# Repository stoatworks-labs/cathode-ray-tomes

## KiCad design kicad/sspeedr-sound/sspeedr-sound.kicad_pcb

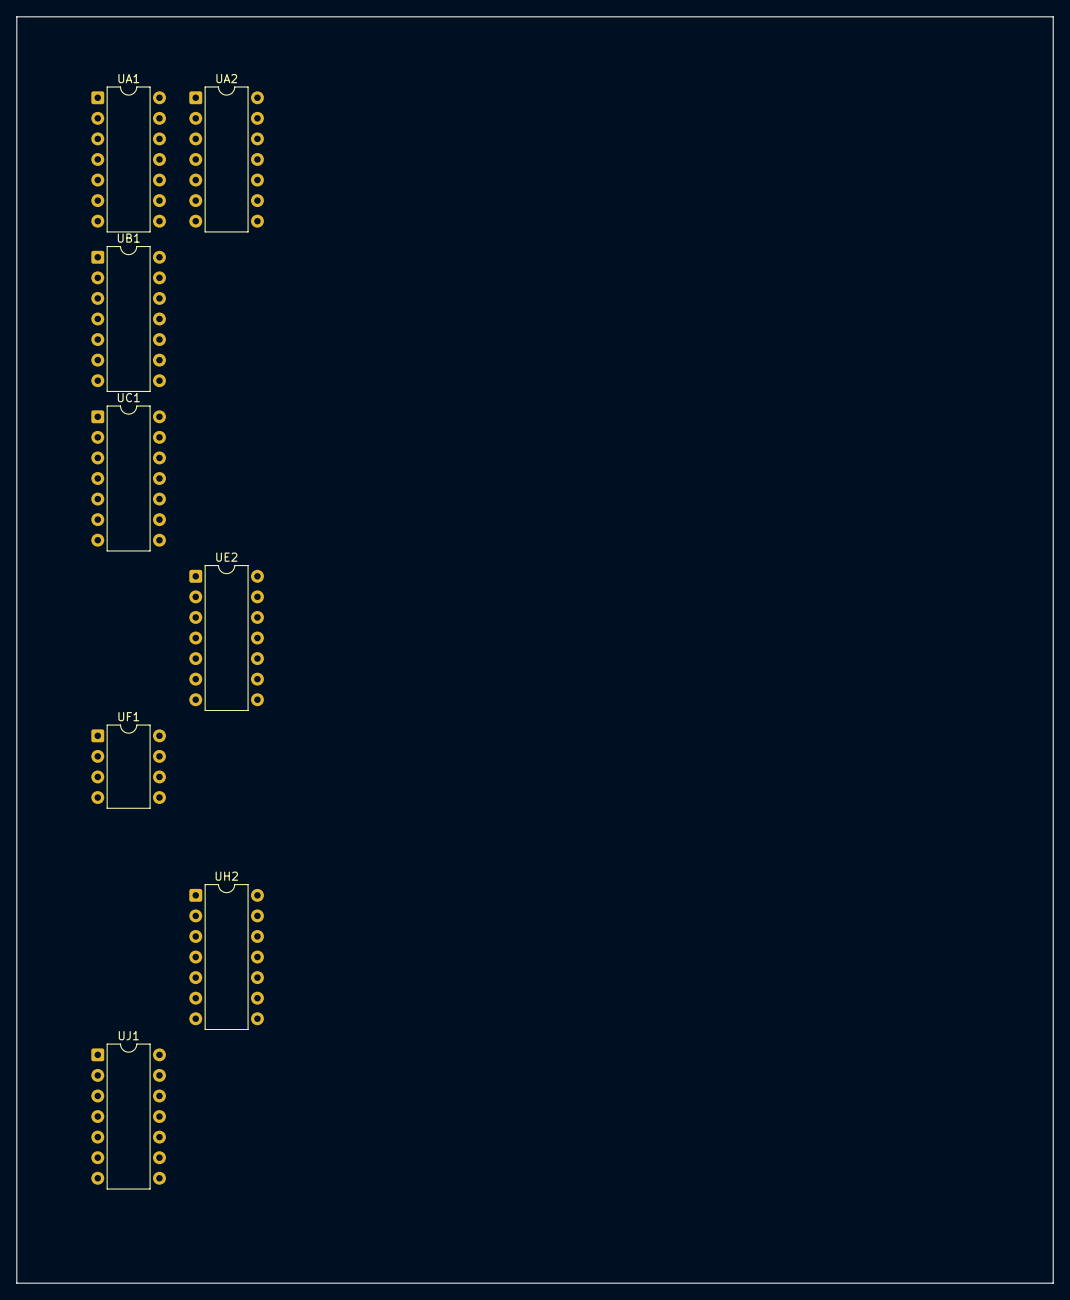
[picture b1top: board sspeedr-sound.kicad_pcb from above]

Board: 2 copper layers, 128.0 x 156.4 mm, 8 parts (0 on the bottom side), 14 nets, no tracks yet.

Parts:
UA1: LM3900; DIP-14_W7.62mm
UA2: CD4016; DIP-14_W7.62mm
UB1: CD4016; DIP-14_W7.62mm
UC1: LM3900; DIP-14_W7.62mm
UE2: CD4016; DIP-14_W7.62mm
UF1: MC3340; DIP-8_W7.62mm
UH2: LM3900; DIP-14_W7.62mm
UJ1: LM3900; DIP-14_W7.62mm

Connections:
+5V: UA1.14, UA2.14, UB1.14, UC1.14, UE2.14, UF1.8, UH2.14
GND: UA1.7, UA2.1, UA2.7, UB1.7, UC1.7, UE2.7, UF1.3, UH2.7, UJ1.7
NOISE_CR_1: UE2.5, UE2.12
unnamed: UE2.10, UH2.9
unnamed: UE2.8, UH2.4
unnamed: UA2.3, UA2.8
unnamed: UE2.4, UJ1.4
unnamed: UA1.5, UB1.13
unnamed: UA1.10, UB1.5
unnamed: UB1.12, UC1.5
unnamed: UA2.4, UC1.11
unnamed: UA1.2, UB1.2
unnamed: UA1.13, UB1.3
unnamed: UB1.11, UC1.2

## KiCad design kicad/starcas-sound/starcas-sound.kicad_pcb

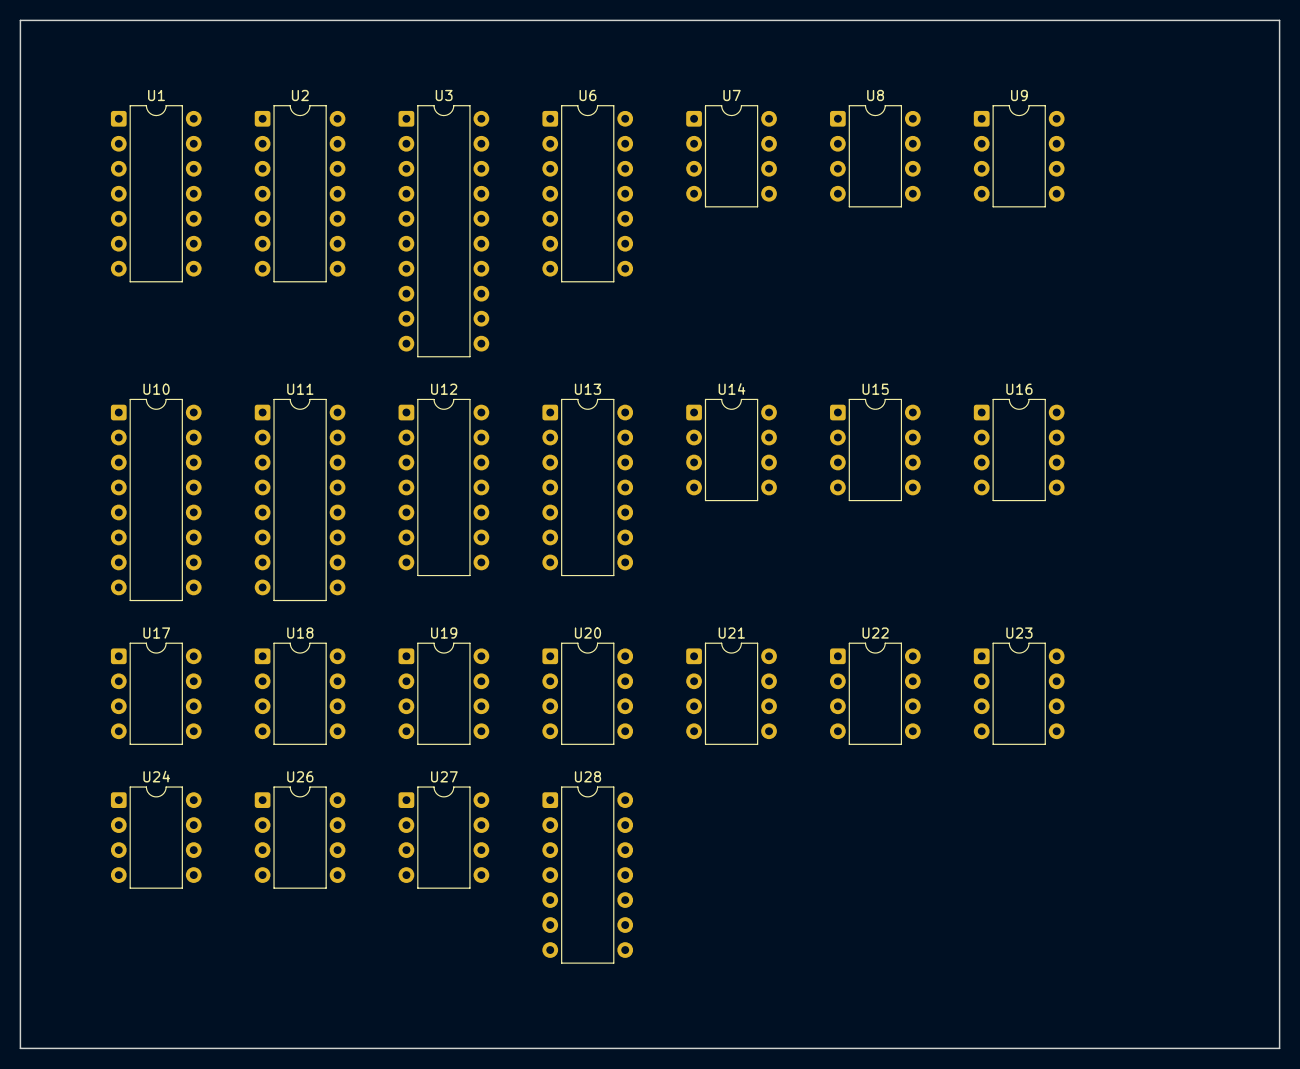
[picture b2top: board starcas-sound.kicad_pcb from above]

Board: 2 copper layers, 128.0 x 104.5 mm, 25 parts (0 on the bottom side), 37 nets, no tracks yet.

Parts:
U1: 7414; DIP-14_W7.62mm
U2: 74LS164; DIP-14_W7.62mm
U3: 74LS377; DIP-20_W7.62mm
U6: 7406; DIP-14_W7.62mm
U7, U8, U15, U26, U27: TL081; DIP-8_W7.62mm
U9, U17: LM566; DIP-8_W7.62mm
U10, U11: 74LS163; DIP-16_W7.62mm
U12, U13: 74LS393; DIP-14_W7.62mm
U14: S2688; DIP-8_W7.62mm
U16, U23, U24: LM555; DIP-8_W7.62mm
U18, U19, U20, U21, U22: CA3080; DIP-8_W7.62mm
U28: 74LS107; DIP-14_W7.62mm

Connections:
+5V: U1.14, U2.14, U3.20, U6.14, U10.16, U11.16, U12.14, U13.14, U16.4, U16.8, U23.8, U24.8, U28.14
+15V: U7.7, U8.7, U14.4, U15.7, U17.8, U18.7, U19.7, U20.7, U21.7, U22.7, U26.7, U27.7
-15V: U7.4, U8.4, U9.1, U15.4, U18.4, U19.4, U20.4, U21.4, U22.4, U26.4, U27.4
BACKGROUND_EN: U3.12, U6.1, U13.2
BL0: U3.19, U6.13
BL1: U3.16, U6.11
BL2: U3.15, U6.9
CLK: U10.2, U11.2, U13.1, U28.12
GND: U1.7, U2.7, U3.1, U3.10, U6.7, U7.3, U9.8, U10.4, U10.5, U10.6, U10.8, U11.3, U11.4, U11.8, U12.7, U12.12, U13.7, U13.12, U14.1, U14.2, U16.1, U17.1, U23.1, U24.1, U27.3, U28.4, U28.7
HI: U2.2, U2.9, U10.3, U10.7, U10.10, U11.5, U11.6, U11.7
NOISE: U15.2, U15.6
unnamed: U16.2, U16.6
unnamed: U23.2, U23.6
unnamed: U24.2, U24.6
unnamed: U26.2, U26.6
unnamed: U6.2, U10.1, U11.1
unnamed: U18.6, U19.6, U20.6, U21.6, U22.6, U26.3
unnamed: U1.1, U1.12
unnamed: U1.2, U2.1
unnamed: U1.4, U3.11
unnamed: U1.5, U1.8
unnamed: U1.6, U2.8
unnamed: U1.3, U1.10
unnamed: U2.3, U3.3
unnamed: U2.4, U3.4
unnamed: U2.5, U3.7
unnamed: U2.6, U3.8
unnamed: U2.10, U3.13
unnamed: U2.11, U3.14
unnamed: U2.12, U3.17
unnamed: U2.13, U3.18
unnamed: U10.9, U11.9, U12.13, U28.2
unnamed: U10.15, U11.10
unnamed: U11.15, U28.1, U28.13
unnamed: U13.6, U13.13
OUT_3: U6.5, U12.2
STAR_EN: U3.6, U23.4, U24.4

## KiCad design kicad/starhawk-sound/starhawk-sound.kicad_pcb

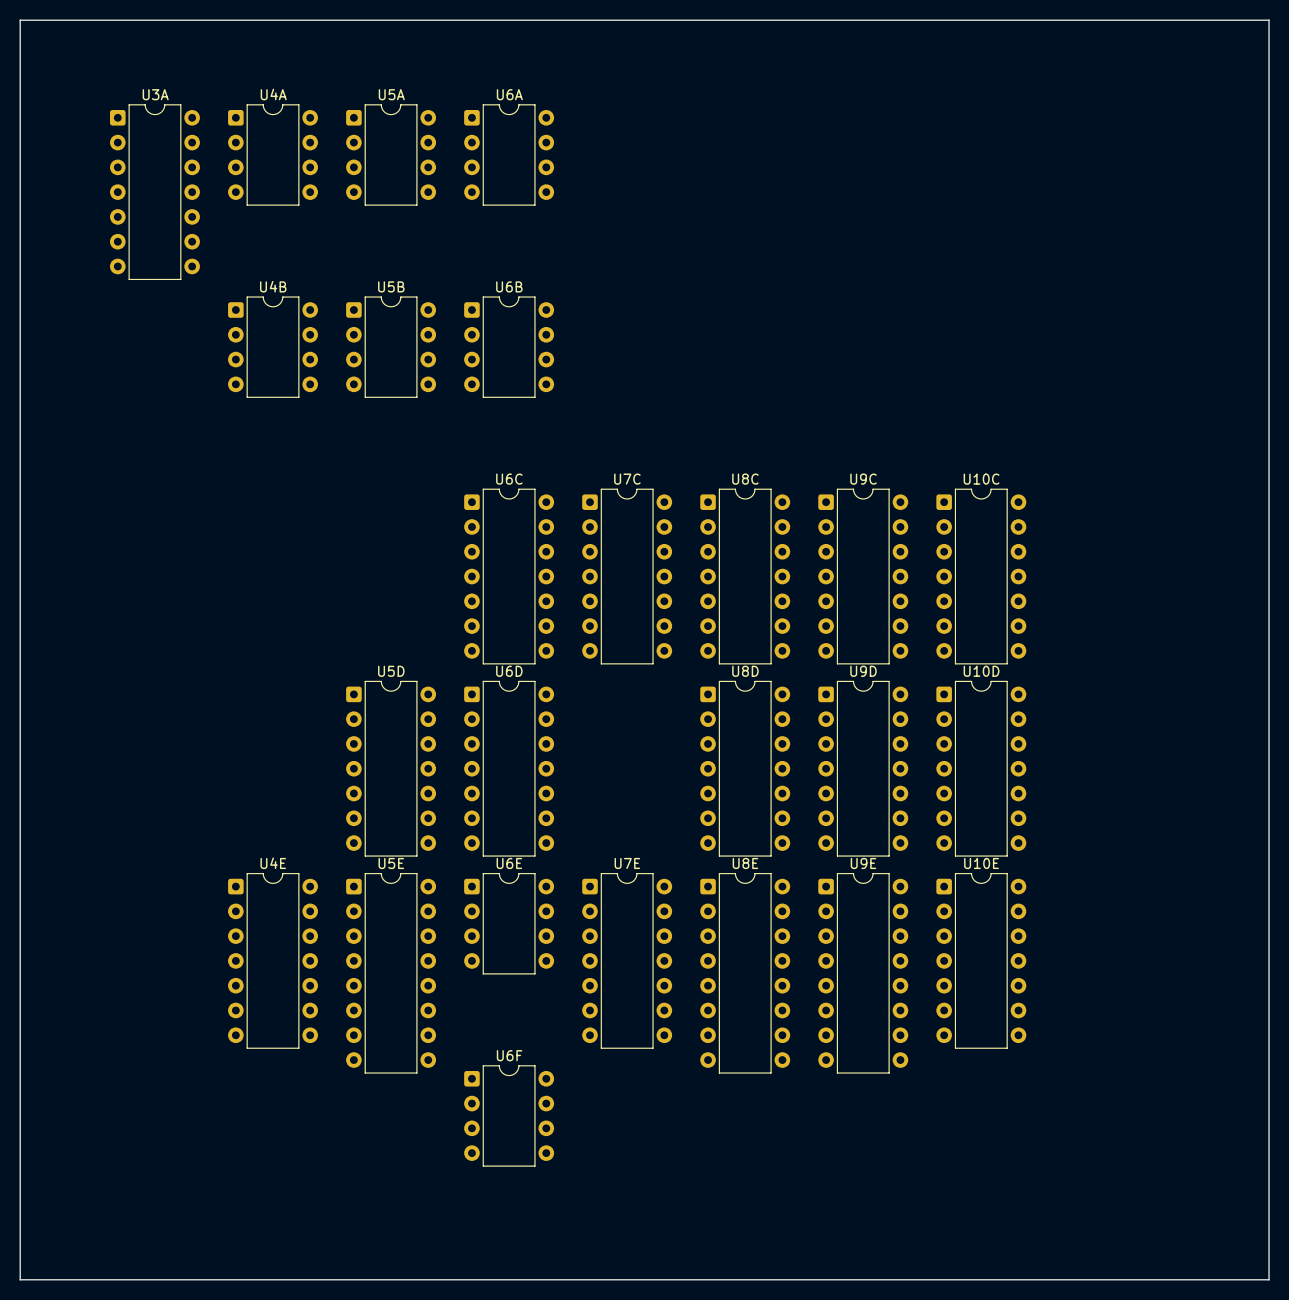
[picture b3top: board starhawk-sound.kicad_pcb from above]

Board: 2 copper layers, 128.0 x 129.1 mm, 25 parts (0 on the bottom side), 53 nets, no tracks yet.

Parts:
U3A: TL182; DIP-14_W7.62mm
U4A, U4B, U5A, U5B, U6B, U6E, U6F: TL081; DIP-8_W7.62mm
U4E, U7E, U10E: 74LS393; DIP-14_W7.62mm
U5D, U6D: LM556; DIP-14_W7.62mm
U5E, U8E: 74S287; DIP-16_W7.62mm
U6A: CA3080; DIP-8_W7.62mm
U6C: 74LS04; DIP-14_W7.62mm
U7C: 7406; DIP-14_W7.62mm
U8C, U8D, U9C, U9D: 74LS164; DIP-14_W7.62mm
U9E: 74LS163; DIP-16_W7.62mm
U10C: 74LS86; DIP-14_W7.62mm
U10D: 74LS21; DIP-14_W7.62mm

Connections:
+5V: U3A.7, U4E.14, U5E.16, U6C.14, U6D.4, U6D.10, U6D.14, U7C.14, U7E.14, U8C.9, U8C.14, U8D.9, U8D.14, U8E.16, U9C.9, U9C.14, U9D.9, U9D.14, U9E.1, U9E.7, U9E.9, U9E.10, U9E.16, U10C.14, U10D.14, U10E.14
+15V: U3A.6, U4A.7, U4B.7, U5A.7, U5B.7, U5D.4, U5D.14, U6A.7, U6B.7, U6E.7, U6F.7
-15V: U3A.9, U4A.4, U4B.4, U5A.4, U5B.4, U6A.4, U6B.4, U6E.4, U6F.4
GND: U3A.8, U4A.3, U4E.2, U4E.7, U4E.12, U5A.3, U5B.3, U5D.7, U5E.1, U5E.8, U5E.13, U6B.3, U6C.7, U6D.7, U7C.7, U7E.2, U7E.7, U7E.12, U8C.7, U8D.7, U8E.1, U8E.8, U8E.13, U9C.7, U9D.7, U9E.8, U10C.7, U10D.7, U10E.7
unnamed: U6D.12, U6D.13
unnamed: U6D.2, U6D.6
unnamed: U3A.1, U4A.2
unnamed: U5D.2, U5D.6
unnamed: U3A.14, U6A.6
unnamed: U4E.1, U6C.12
unnamed: U4E.3, U5E.7
unnamed: U4E.4, U5E.4
unnamed: U4E.5, U5E.6
unnamed: U4E.8, U5E.15
unnamed: U4E.10, U5E.2
unnamed: U4E.11, U5E.3
unnamed: U4E.6, U4E.13, U5E.5
unnamed: U5E.14, U6C.2, U7C.13
unnamed: U6C.4, U7C.11
unnamed: U6C.6, U7C.9, U8E.14
unnamed: U6C.8, U7E.1
unnamed: U7E.3, U8E.7
unnamed: U7E.4, U8E.4
unnamed: U7E.5, U8E.6
unnamed: U7E.8, U8E.15
unnamed: U7E.10, U8E.2
unnamed: U7E.11, U8E.3
unnamed: U7E.6, U7E.13, U8E.5
unnamed: U8C.13, U9C.1, U9C.2
unnamed: U8D.13, U9D.1, U9D.2
unnamed: U10C.1, U10D.8
unnamed: U10C.2, U10C.8
unnamed: U8C.1, U8C.2, U10C.3
unnamed: U10C.5, U10D.6
unnamed: U8D.1, U8D.2, U10C.6
unnamed: U9C.12, U10C.9
unnamed: U9C.10, U10C.10
unnamed: U10C.4, U10C.11
unnamed: U9D.12, U10C.12
unnamed: U9D.10, U10C.13
unnamed: U10D.1, U10E.3
unnamed: U10D.2, U10E.4
unnamed: U10D.4, U10E.5
unnamed: U10D.5, U10E.6
unnamed: U10D.9, U10E.8
unnamed: U10D.10, U10E.9
unnamed: U10D.12, U10E.10
unnamed: U10D.13, U10E.11
unnamed: U6D.5, U8D.8, U9D.8, U9E.2, U10E.1
unnamed: U8D.3, U10E.2
unnamed: U8C.3, U10E.12
unnamed: U8C.8, U9C.8, U9E.15, U10E.13
OUT_3: U3A.5, U6C.3

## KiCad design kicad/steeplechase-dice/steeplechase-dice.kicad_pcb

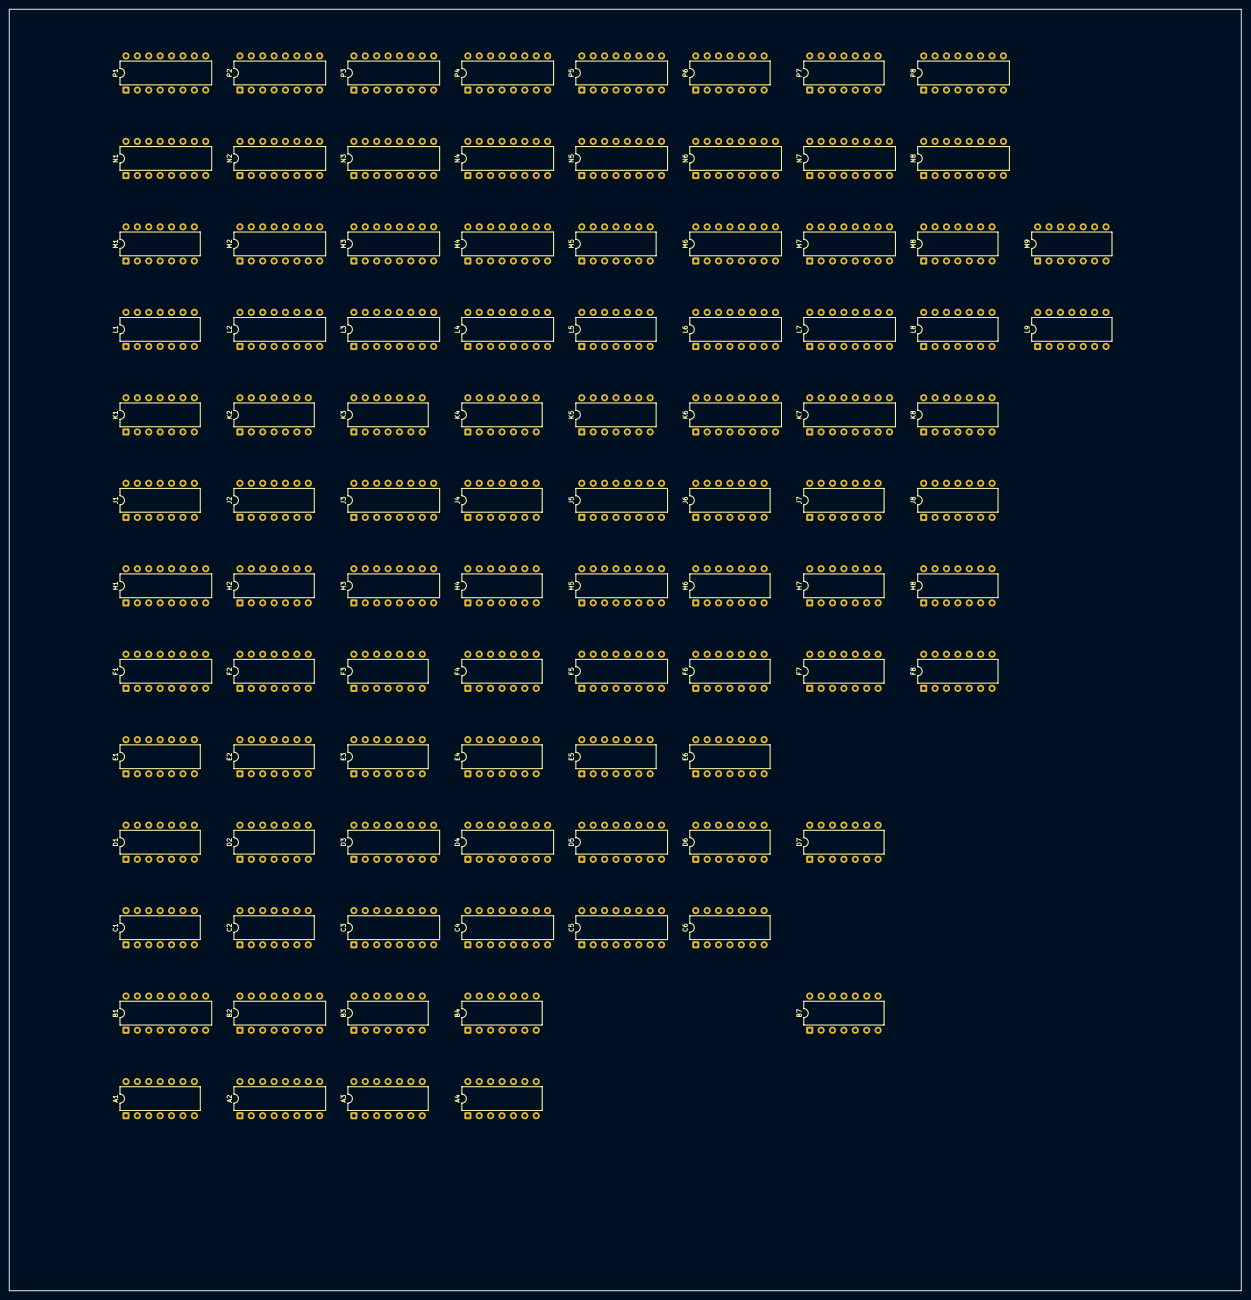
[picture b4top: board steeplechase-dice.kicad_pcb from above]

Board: 2 copper layers, 274.6 x 285.6 mm, 94 parts (0 on the bottom side), 273 nets, no tracks yet.

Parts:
A1: 74164; DIP-14_W7.62mm
A2: 9316; DIP-16_W7.62mm
A3: 7400; DIP-14_W7.62mm
A4: 7474; DIP-14_W7.62mm
B1, B2: 9316; DIP-16_W7.62mm
B3: 7420; DIP-14_W7.62mm
B4: 7408; DIP-14_W7.62mm
B7: 74107; DIP-14_W7.62mm
C1: 74164; DIP-14_W7.62mm
C2: 7474; DIP-14_W7.62mm
C3: 9316; DIP-16_W7.62mm
C4: 74S287; DIP-16_W7.62mm
C5: 74165; DIP-16_W7.62mm
C6: 7420; DIP-14_W7.62mm
D1, D7: 7400; DIP-14_W7.62mm
D2, D6: 7404; DIP-14_W7.62mm
D3: 9316; DIP-16_W7.62mm
D4: 74S287; DIP-16_W7.62mm
D5: 74165; DIP-16_W7.62mm
E1, E2, E3, E5: 7474; DIP-14_W7.62mm
E4, E6: 7402; DIP-14_W7.62mm
F1: 9316; DIP-16_W7.62mm
F2: 7427; DIP-14_W7.62mm
F3: 7410; DIP-14_W7.62mm
F4: 7486; DIP-14_W7.62mm
F5: 9312; DIP-16_W7.62mm
F6, F8: 7474; DIP-14_W7.62mm
F7: 7493; DIP-14_W7.62mm
H1, H3: 9316; DIP-16_W7.62mm
H2: 7474; DIP-14_W7.62mm
H4: 7400; DIP-14_W7.62mm
H5: 9312; DIP-16_W7.62mm
H6, H7: 7402; DIP-14_W7.62mm
H8: 7404; DIP-14_W7.62mm
J1: 7432; DIP-14_W7.62mm
J2: 7402; DIP-14_W7.62mm
J3: 9301; DIP-16_W7.62mm
J4: 7474; DIP-14_W7.62mm
J5: 9312; DIP-16_W7.62mm
J6, J7: 7411; DIP-14_W7.62mm
J8: 7486; DIP-14_W7.62mm
K1, K5, K8: 7474; DIP-14_W7.62mm
K2, K4: 7402; DIP-14_W7.62mm
K3: 7404; DIP-14_W7.62mm
K6, K7: 9316; DIP-16_W7.62mm
L1: 7404; DIP-14_W7.62mm
L2, L3, L4, L6, L7: 9316; DIP-16_W7.62mm
L5, L8: 7474; DIP-14_W7.62mm
L9: 7414; DIP-14_W7.62mm
M1, M9: 7404; DIP-14_W7.62mm
M2, M3, M4, M6, M7: 9316; DIP-16_W7.62mm
M5, M8: 7474; DIP-14_W7.62mm
N1, N2, N3, N4: 9316; DIP-16_W7.62mm
N5: 9301; DIP-16_W7.62mm
N6, N7: 74175; DIP-16_W7.62mm
N8: 9312; DIP-16_W7.62mm
P1, P2, P3, P4, P5: 9316; DIP-16_W7.62mm
P6: 7430; DIP-14_W7.62mm
P7: 7404; DIP-14_W7.62mm
P8: 9312; DIP-16_W7.62mm

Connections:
+5V: A1.14, A2.16, A3.14, A4.14, B1.16, B2.16, B3.14, B4.14, B7.14, C1.14, C2.14, C3.16, C5.16, C6.14, D1.14, D2.14, D3.16, D5.16, D6.14, D7.14, E1.14, E2.14, E3.14, E4.14, E5.14, E6.14, F1.16, F2.14, F3.14, F4.14, F5.16, F6.14, F7.5, F8.14, H1.16, H2.14, H3.16, H4.14, H5.16, H6.14, H7.14, H8.14, J1.14, J2.14, J3.16, J4.14, J5.16, J6.14, J7.14, J8.14, K1.14, K2.14, K3.14, K4.14, K5.14, K6.16, K7.16, K8.14, L1.14, L2.16, L3.16, L4.16, L5.14, L6.16, L7.16, L8.14, L9.14, M1.14, M2.16, M3.16, M4.16, M5.14, M6.16, M7.16, M8.14, M9.14, N1.16, N2.16, N3.16, N4.16, N5.16, N6.16, N7.16, N8.16, P1.16, P2.16, P3.16, P4.16, P5.16, P6.14, P7.14, P8.16
A: N6.10, P5.6
A1-1: A1.1, A1.2, F4.3
A1-8: A1.8, B1.9, C1.8, D1.8
A1-11: A1.11, B1.6, F4.1
A2-7: A2.7, A2.10, C2.9
A2-15: A2.15, B2.7, B2.10, D1.10
A3-3: A3.3, B4.12
A3-5: A3.5, A3.8
A3-6: A3.6, B3.10
A3-11: A3.11, B3.12
A3-13: A3.13, F4.8
A4-2: A4.2, F2.8
A4-3: A4.3, F2.12
A4-11: A4.11, D6.8, N6.9, N7.9
ATTRACT: D6.3, D6.11, F7.2, F7.3, F8.6
ATTRACT_n: A2.1, C1.9, D6.4, F3.11, K8.2, K8.12, L8.2, L8.12, M8.2, M8.12
A_n: N6.11, P5.5
B: N6.15, P5.4
B1-1: B1.1, C1.11, J1.5
B1-4: B1.4, B2.12
B1-5: B1.5, B2.13
B1-7: B1.7, C2.8, C2.12
B1-10: B1.10, B2.14, D1.9
B2-9: B2.9, D2.8
B2-15: B2.15, D1.13, D2.9
B3-8: B3.8, B4.9
B3-13: B3.13, B4.11
B4-1: B4.1, P1.14
B4-2: B4.2, N1.12
B4-3: B4.3, J4.11
B4-5: B4.5, D1.5, F1.15
B4-10: B4.10, F3.13, F5.15
B7-9: B7.9, H3.15, L1.11
BUFFERED_CLOCK: A2.2, B1.2, B2.2, C2.11, L1.12
BUG_TRIG_n: D6.6, F6.10, N1.1, P1.1
C: A4.9, P5.3
C1-1: C1.1, C1.2, J1.6
C2-10: C2.10, D1.11
C3-6: C3.6, D3.3, D3.4, D3.5, E2.6
C4-1: C4.1, D4.1, E4.13
C4-2: C4.2, D4.2, E4.4
C4-9: C4.9, C5.14, D5.14
C4-10: C4.10, C5.13, D5.13
C4-11: C4.11, C5.12, D5.12
C4-12: C4.12, C5.11, D5.11
C4-15: C4.15, D4.15, E4.2, E4.12, H4.11
C5-1: C5.1, J1.8, J1.13
C5-3: C5.3, D4.12, D5.3
C5-4: C5.4, D4.11, D5.4
C5-5: C5.5, D4.10, D5.5
C5-6: C5.6, D4.9, D5.6
C5-9: C5.9, D5.10
C5-15: C5.15, D5.15, E5.9
C6-6: C6.6, H8.9
C6-8: C6.8, F5.10
C6-13: C6.13, N8.14
CLOCK: F1.2, H1.2, H2.3, K1.5, K1.11, K2.8
COIN: F6.3, F6.11, H8.5, J8.11
D1-2: D1.2, M1.9, P5.15
D1-4: D1.4, F1.7, H1.15
D2-1: D2.1, D2.3, E1.9
D5-1: D5.1, J1.11
D5-9: D5.9, F3.2
D6-5: D6.5, E6.13
D6-9: D6.9, E1.1, H4.3
D7-2: D7.2, D7.6
D7-3: D7.3, D7.4
D7-5: D7.5, H4.6
E1-8: E1.8, E1.12
E2-2: E2.2, E2.8
E4-1: E4.1, E4.5
E4-6: E4.6, H5.15
E5-2: E5.2, H8.6
E5-6: E5.6, E6.3, E6.5
E5-8: E5.8, F3.1
E5-11: E5.11, P8.14
E6-2: E6.2, E6.9, F6.5, F6.12
E6-6: E6.6, F6.9
E6-10: E6.10, E6.11
F1: H3.14, J3.15
F2: H3.13, J3.14
F2-13: F2.13, J5.15
F3-6: F3.6, N8.10
F3-8: F3.8, J3.2
F4: F3.4, H3.12, J3.1
F4-2: F4.2, J2.1
F4-4: F4.4, J8.6
F4-5: F4.5, H4.8
F6-1: F6.1, F6.13
F8: F3.5, F3.10, H3.11
F8-3: F8.3, H8.12
F16: B7.5, J1.2
FALL1: H6.8, J5.2, J6.5, L5.5
FALL2: H7.8, J5.3, J7.5, L5.9
FALL3: H6.3, J5.4, J6.13, K5.5
FALL4: H7.3, J5.5, J7.13, K5.9
FALL5: H7.6, J5.6, J7.9, M5.9
FALL6: H6.6, J5.7, J6.9, M5.5
FINISH_LINE: A3.12, B4.6, H4.4
FWD1: K2.5, K3.12
FWD2: K3.4, K4.6
FWD3: K3.10, K4.8
FWD4: K2.2, K3.6
FWD5: K2.11, K3.8
FWD6: K3.2, K4.3
FWD7_n: J1.3, N1.3
GALLOP_A: E4.3, F4.11
GALLOP_B: E4.11, F4.6
GAME_RESET1_n: E5.5, E6.12, K5.11, L2.1, L5.3, M2.1, N2.1, P2.1
GAME_RESET2_n: E6.1, L3.1, L5.11, M3.1, M5.11, N3.1, P3.1
GAME_RESET3_n: E6.4, K5.3, L4.1, M4.1, M5.3, N4.1, P4.1
GND: A1.7, A2.8, A3.7, A4.7, B1.3, B1.8, B2.3, B2.4, B2.6, B2.8, B3.7, B4.7, B7.7, C1.7, C2.7, C3.3, C3.4, C3.5, C3.8, C4.13, C4.14, C5.8, C5.10, C6.7, D1.7, D2.7, D3.6, D3.8, D4.13, D4.14, D5.8, D6.7, D7.7, E1.7, E2.7, E3.7, E4.7, E5.7, E5.12, E6.7, F1.3, F1.4, F1.6, F1.8, F2.7, F3.7, F4.7, F5.1, F5.8, F6.7, F7.10, F8.7, H1.8, H2.7, H3.3, H3.4, H3.6, H3.8, H4.7, H5.1, H5.8, H6.7, H7.7, H8.7, J1.7, J2.7, J3.8, J4.7, J4.12, J5.1, J5.8, J5.9, J6.7, J7.7, J8.7, K1.7, K2.7, K3.7, K4.7, K5.2, K5.7, K5.12, K6.6, K6.8, K7.6, K7.8, K8.7, L1.7, L2.5, L2.6, L2.8, L3.5, L3.6, L3.8, L4.5, L4.6, L4.8, L5.2, L5.7, L5.12, L6.6, L6.8, L7.6, L7.8, L8.7, L9.7, M1.7, M2.8, M3.8, M4.8, M5.2, M5.7, M5.12, M6.6, M6.8, M7.6, M7.8, M8.7, M9.7, N1.4, N1.5, N1.6, N1.8, N2.5, N2.6, N2.8, N3.5, N3.6, N3.8, N4.5, N4.6, N4.8, N5.8, N6.8, N7.8, N8.1, N8.8, N8.9, P1.8, P2.8, P3.8, P4.8, P5.8, P6.7, P7.7, P8.1, P8.8
H1: H1.7, H1.10, H2.5
H2: F4.9, H1.14
H2-2: H2.2, H2.6
H3-9: H3.9, L1.10
H4-1: H4.1, P6.8
H4-12: H4.12, J5.14
H4-13: H4.13, H5.14
H6-2: H6.2, K6.15, K8.1, M9.1
H6-5: H6.5, M6.15, M8.1, M9.3
H6-9: H6.9, L6.15, L8.1, M9.11
H7-2: H7.2, K7.15, K8.13, M9.13
H7-5: H7.5, M7.15, M8.13, M9.5
H7-9: H7.9, L7.15, L8.13, M9.9
H8: B4.4, H1.12
H16: F1.10, H1.11, J1.9
H32: A4.12, C4.3, D4.3, F1.14, F2.9, H2.11, J1.12
H64: A3.2, F1.13, F2.10, H2.12, J2.9, N6.13
H128: F1.12, F2.11, N6.12
H256: E5.3, E5.10, F1.11, J1.10, K1.12, K1.13, L1.9
H256_n: A3.1, H2.10, L1.8
HALF_TRACK_CLOCK: D2.4, F7.14, K6.2, K7.2, L6.2, L7.2, M6.2, M7.2
HBLANK_n: C6.12, H2.9, J2.8
HCLOCK1: M1.10, N2.2, N3.2, P2.2, P3.2
HCLOCK2: L2.2, M1.2, M2.2, N4.2, P4.2
HCLOCK3: L3.2, L4.2, M1.4, M3.2, M4.2
HCLOCK4: C5.2, D5.2, M1.12, N1.2, P1.2
HIT1_n: L5.4, L6.1, N5.12
HIT2_n: L5.10, L7.1, N5.11
HIT3_n: K5.4, K6.1, N5.10
HIT4_n: K5.10, K7.1, N5.9
HIT5_n: M5.10, M7.1, N5.3
HIT6_n: M5.4, M6.1, N5.4
HIT_TRIGGER_n: A4.5, N5.2
HORSES: H4.5, J2.4
HORSES_n: B4.13, F2.2, F3.12, J2.5, J2.6
HRESET_n: A4.4, D1.6, F1.9, J2.3
HSYNC: C2.3, C3.2, D3.2, J1.4, J2.10
J1-1: J1.1, J3.4
J3-3: J3.3, K3.1
J3-9: J3.9, K3.9
J3-10: J3.10, K3.5
J3-11: J3.11, K3.11
J3-12: J3.12, K3.3
J3-13: J3.13, K3.13
J4-3: J4.3, K4.13
J4-8: J4.8, K4.11
J4-10: J4.10, M1.6, N1.9
J6-2: J6.2, K6.14
J6-4: J6.4, L6.14
J6-10: J6.10, M6.14
J7-2: J7.2, K7.14
J7-4: J7.4, L7.14
J7-10: J7.10, M7.14
JUMP1: H5.2, H6.10
JUMP2: H5.3, H7.10
JUMP3: H5.4, H6.1
JUMP4: H5.5, H7.1
JUMP5: H5.6, H7.4
JUMP6: H5.7, H6.4
JUMP7: H5.9, J4.5
K1-2: K1.2, K1.6, L1.13
K1-3: K1.3, L1.4
K1-8: K1.8, K2.9
K2-1: K2.1, L2.3
K2-4: K2.4, N2.3
K2-10: K2.10, M1.1, M1.3, M1.11, M1.13
K2-13: K2.13, L3.3
K4-1: K4.1, L4.3
K4-4: K4.4, N3.3
K4-10: K4.10, N4.3
K5-1: K5.1, K6.7, M9.2
K5-13: K5.13, K7.7, M9.12
K6-9: K6.9, K8.6
K7-9: K7.9, K8.8
K8-3: K8.3, L9.10
K8-11: K8.11, L9.12
L2-15: L2.15, M2.7, M2.10
L3-15: L3.15, M3.7, M3.10
L4-15: L4.15, M4.7, M4.10
L5-1: L5.1, L6.7, M9.10
L5-13: L5.13, L7.7, M9.8
L6-9: L6.9, L8.6
L7-9: L7.9, L8.8
L8-3: L8.3, L9.6
L8-11: L8.11, L9.8
L9-2: L9.2, M8.11
L9-4: L9.4, M8.3
LEAD1: L6.5, N7.2, N8.2
LEAD1_n: L6.4, N7.3
LEAD2: L7.5, N7.7, N8.3
LEAD2_n: L7.4, N7.6
LEAD3: K6.5, N7.10, N8.4
LEAD3_n: K6.4, N7.11
LEAD4: K7.5, N7.15, N8.5
LEAD4_n: K7.4, N7.14
LEAD5: M7.5, N6.2, N8.6
LEAD5_n: M7.4, N6.3
LEAD6: M6.5, N6.7, N8.7
LEAD6_n: M6.4, N6.6
LEAD7_n: E1.6, K6.3, K7.3, L6.3, L7.3, M6.3, M7.3
M1-8: M1.8, P5.9
M5-1: M5.1, M6.7, M9.4
M5-13: M5.13, M7.7, M9.6
M6-9: M6.9, M8.6
M7-9: M7.9, M8.8
N1-15: N1.15, P1.7, P1.10
N2-15: N2.15, P2.7, P2.10
N3-15: N3.15, P3.7, P3.10
N4-15: N4.15, P4.7, P4.10
PICKET_LINE: B1.15, B3.1
PICKET_n: B3.6, B3.9, F2.1, K4.12
PLAY4: F5.3, F5.6, F6.6
PLAY6: F5.4, F5.7, F6.8
Q: D7.1, F8.1, F8.2, H8.2, H8.3
Q_n: F3.3, F6.2, H8.4
RAND: E2.11, H8.10, J2.2
REV1: J6.6, K2.6, N2.4
REV2: J7.6, K4.5, N3.4
REV3: J6.12, K4.9, N4.4
REV4: J7.12, K2.3, L2.4
REV5: J7.8, K2.12, L3.4
REV6: J6.8, K4.2, L4.4
T1: A2.14, A3.9
T2: A2.13, A3.10
TC1: N7.4, P2.15, P7.1, P8.2
TC1_n: N2.9, P6.4, P7.2
TC2: N7.5, P3.15, P7.3, P8.3
TC2_n: N3.9, P6.2, P7.4
TC3: N7.12, P4.15, P7.5, P8.4
TC3_n: N4.9, P6.1, P7.6
TC4: M2.15, N7.13, P7.9, P8.5
TC4_n: L2.9, P6.11, P7.8
TC5: M3.15, N6.4, P7.11, P8.6
TC5_n: L3.9, P6.12, P7.10
TC6: M4.15, N6.5, P7.13, P8.7
TC6_n: L4.9, P6.3, P7.12
TC7: C6.1, C6.2, C6.4, E1.3, M1.5, P1.15, P8.9
TRACK: A3.4, C3.15, D1.1, D3.7, D3.10
TRACK_CLOCK: D1.12, D2.6, J6.1, J6.3, J6.11, J7.1, J7.3, J7.11
TRACK_CLOCK_n: D1.3, D2.5, E1.11
V1: C2.5, C3.7, C3.10, C4.5, D4.5
V1_n: C2.2, C2.6
V2: C3.14, C4.6, D4.6, F4.10
V4: B3.2, C3.13, C4.7, D4.7, E3.11
V8: B3.4, C3.12, C4.4, D4.4
V16: B3.5, C3.11, C6.9, P5.2
V32: D3.14, E3.3, F5.11, H5.11, J5.11, J8.4, N5.15, N8.11, P8.11
V64: D3.13, F4.12, F5.12, H4.9, H5.12, J5.12, N5.14, N8.12, P8.12
V128: D3.12, F5.13, H5.13, J5.13, N5.1, N8.13, P8.13
V256: D2.11, D3.11, E3.1, E3.2, E3.12, E3.13, P5.10
V256_n: D2.10, H5.10, J2.11, J5.10, P8.10
VBLANK_n: C6.10, E3.5
VCC: A1.9, A2.9, A4.1, A4.10, A4.13, B2.1, B2.5, B7.8, B7.10, B7.11, C2.1, C2.4, C2.13, C3.1, D3.1, E1.2, E1.4, E1.10, E1.13, E2.1, E2.4, E2.10, E2.12, E3.4, E3.10, E5.1, E5.4, E5.13, F1.1, F1.5, F5.2, F5.5, F5.9, F6.4, F8.4, H1.1, H1.9, H2.1, H2.4, H2.13, H3.1, H3.7, H3.10, J4.2, J4.4, J4.13, J8.10, K1.1, K1.4, K1.10, K6.10, K7.10, K8.4, K8.10, L2.7, L2.10, L3.7, L3.10, L4.7, L4.10, L6.10, L7.10, L8.4, L8.10, M2.9, M3.9, M4.9, M6.10, M7.10, M8.4, M8.10, N1.7, N1.10, N2.7, N2.10, N3.7, N3.10, N4.7, N4.10, N6.1, N7.1, P1.9, P2.9, P3.9, P4.9, P5.1, P5.7, P6.5, P6.6
VF1: E3.9, H3.2, J2.12, J4.1
VRESET: C6.5, D2.13, D3.15, E2.3, F3.9, H4.2
VRESET_n: C3.9, D2.12, D3.9, E2.13
X1: F7.1, F7.12
X3: F4.13, F7.8, H4.10
X4: F7.11, J8.9
X4_n: J8.5, J8.8

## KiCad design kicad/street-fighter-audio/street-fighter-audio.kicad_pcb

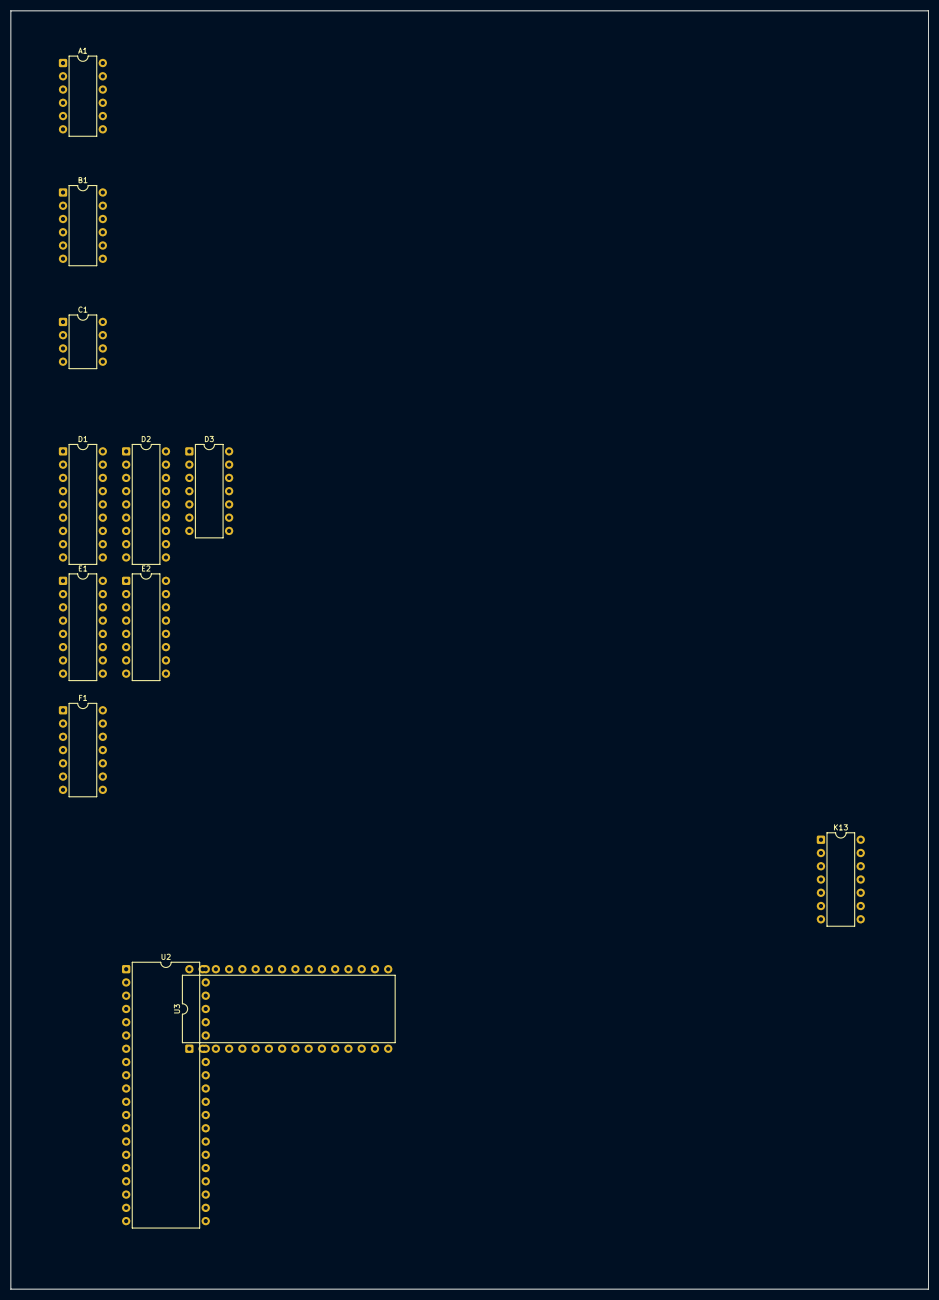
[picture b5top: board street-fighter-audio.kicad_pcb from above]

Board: 2 copper layers, 175.8 x 244.9 mm, 12 parts (0 on the bottom side), 23 nets, no tracks yet.

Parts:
A1: HA13001; DIP-12_W7.62mm
B1: HA13001; DIP-12_W7.62mm
C1: LM358; DIP-8_W7.62mm
D1, D2: OKI-M5205; DIP-18_W7.62mm
D3: LM324; DIP-14_W7.62mm
E1, E2: 74LS174; DIP-16_W7.62mm
F1: 74LS32; DIP-14_W7.62mm
K13: 74LS74; DIP-14_W7.62mm
U2: Z80CPU; DIP-40_W15.24mm
U3: 27C1000; DIP-32_W15.24mm

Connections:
/CD0: D1.4, E1.15
/CD1: D1.5, E1.12
/CD2: D1.6, E1.10
/CD3: D1.7, E1.7
/CD4: D2.4, E2.7
/CD5: D2.5, E2.10
/CD6: D2.6, E2.12
/CD7: D2.7, E2.15
/D0: E1.14, E2.14, U3.13
/D1: E1.13, E2.13, U3.14
/D2: E1.11, E2.11, U3.15
/D3: E1.6, E2.6, U3.17
/D6: E1.4, E2.4, U3.20
/D7: E1.3, E2.3, U3.21
/RSTH: D2.15, F1.8, F1.10
/RSTL: E1.2, F1.5
unnamed: C1.1, C1.2
unnamed: C1.6, C1.7
unnamed: D1.15, F1.6
unnamed: D1.14, K13.9
unnamed: D2.14, K13.8, K13.12
VCC: A1.10, B1.10, D1.2, D1.3, D1.18, D2.2, D2.3, D2.18, E1.16, E2.16, F1.14, K13.10, K13.13, K13.14, U2.11
VSS: A1.1, A1.4, A1.9, B1.1, B1.4, B1.7, B1.9, D1.9, D1.12, D2.9, D2.12, E1.8, E2.8, F1.7, K13.7
